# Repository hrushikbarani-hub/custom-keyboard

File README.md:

# NEXUS 2x3 Wired Macro Pad

A compact six-key wired macro pad with a small I2C OLED screen.

## Design direction

- Layout: 2 rows x 3 columns, six MX-style keys
- Controller: Hack Club Orpheus Pico 2, USB-C, Pico-compatible footprint
- Display: Waveshare 0.91-inch OLED SKU 14657, SSD1306 128x32, GP4/GP5
- Firmware: USB HID macro layers
- PCB: custom KiCad board
- Case: two-piece 3D-printed case

## Initial layers

NEXUS: Wake PC, open NEXUS, display standby, microphone toggle, Jellyfin, Pi-hole/Tailscale status.

Media: previous, play/pause, next, volume down, volume up, mute.

## Build status

- [x] Concept, layout, pin budget, BOM, and grant draft
- [x] Confirm exact controller, OLED, switch, and socket part numbers
- [x] KiCad schematic (ERC clean)
- [x] PCB routing (DRC/connectivity/parity clean)
- [x] Case CAD (v1.1; physical fit pending)
- [x] Firmware source prepared
- [ ] Physical assembly and testing

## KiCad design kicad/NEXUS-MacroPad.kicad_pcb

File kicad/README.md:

# NEXUS 2x3 macro pad — KiCad 10

Open `NEXUS-MacroPad.kicad_pro`. Editable schematic, fully routed two-layer PCB, and project-local footprints are included. `manufacturing/` contains the two copper layers, both masks and silkscreens, board outline, and separate plated/non-plated Excellon drills. No solder-paste files are needed for this through-hole design.

## Fabrication and assembly

- PCB: 60 x 66 mm bounding box; chamfered outline with two OLED clamp reliefs. Two copper layers, 1.6 mm FR4, 0.25 mm traces/clearance, 0.8/0.4 mm vias. Order only after confirming the selected hardware dimensions.
- Six PCB-mount Cherry-MX-compatible switches, 19.05 mm pitch. Plate mounting supplies mechanical retention; switch solder joints locate the PCB. No independent PCB mounting screws are used.
- Six 1N4148 DO-35 diodes with 7.62 mm lead pitch. Cathode/band is the square pad and goes to the row. Front keys are SW1–3; rear keys SW4–6.
- Non-wireless Pico-compatible module socketed **under** the board, component side facing the case floor, USB facing the rear. Use two 1x20, 2.54 mm socket strips plus matching module headers. The host-board footprint courtyard describes socket rows, not the elevated underside module body. Do not install a Pico W: its antenna clearance is not provided.
- J1 is four direct-solder wire pads, not a header or a direct OLED-module footprint. Pin 1 GND, pin 2 3.3 V, pin 3 SCL, pin 4 SDA. Check the actual OLED pin order; use 3.3 V only. Solder insulated flexible leads directly to the pads and provide strain relief. Do not fit a vertical header: it would hit the lid. Keep solder/wire height below 1.2 mm above the PCB.
- R1 and R2 are optional 4.7k through-hole pullups on the PCB underside, marked DNP. Leave them empty if the display already has I2C pullups; populate only if needed. Top-side mounting would overlap the OLED envelope.
- Avoid long switch/diode leads on the underside where they approach the raised controller. Trim and inspect before inserting the module. Do not connect an external 5 V supply.

## Firmware pin assignment

| Function | GPIO | Pico physical pad |
|---|---|---|
| OLED SDA | GP4 | 6 |
| OLED SCL | GP5 | 7 |
| Front row ROW0 | GP6 | 9 |
| Rear row ROW1 | GP7 | 10 |
| Left column COL0 | GP8 | 11 |
| Middle column COL1 | GP9 | 12 |
| Right column COL2 | GP10 | 14 |

Scan rows low with column input pullups (COL2ROW). The schematic deliberately leaves unused module pins unconnected. Pico module ground pads are internally common; all seven carrier ground pads are also routed.

## Case compatibility and limits

Use the revised **v1.2** case in the [Onshape document](https://cad.onshape.com/documents/93b46cd1c225a7c1c0317dbe/w/328820a536ad539164365b4e/e/89c11f70e4b29e71ba5d3f40). The old v1 OLED bridge is superseded by two side clamps, which clear the PCB reliefs. Six underside diode pockets provide clearance after correcting the switch stack. Four printed bodies: base, plate, two clamps. Older case exports are superseded.

Case coordinates are front-left origin. PCB X = 100 + case X; PCB Y = 178 - case Y. Assembled PCB top is case Z = 21 mm, bottom 19.4 mm; the plate top is Z = 26 mm, and the local underside Z = 24.5 mm. MX seating uses 5 mm from plate TOP to PCB top (3.5 mm below the 1.5 mm clip region). STEP uses XY aligned to the case and requires a +21 mm Z translation. The earlier 19.5/17.9 mm stack was incorrect and is superseded. See the [Cherry mechanical drawing](https://www.farnell.com/datasheets/1792245.pdf), mounting options on page 2.

The STEP uses a generic Raspberry Pi Pico, not the exact USB-C Orpheus board. Installed MX switch 3D models are missing; their native footprint geometry is present. Onshape now checks the exact PCB outline plus 20 nominal electronics envelopes against the case and each other. The USB-plug/controller bounding-box overlap is intentionally excluded because a plug engages the connector; exact connector mating is not modeled. Nominal checks passed, but these are not a tolerance analysis or an exact component assembly. Actual socket height, USB plug, OLED module, switch variant, and insert pilot still require confirmation. No physical prototype has been tested. Toggle 'Show electronics fit envelopes' in the case feature to inspect; keep it OFF for printing/exporting case parts.

KiCad ERC, DRC, connectivity, and schematic-to-PCB parity reports are included. No reported issues were suppressed to obtain a pass. Manufacturing exports are design outputs, not an instruction to order without the above checks.

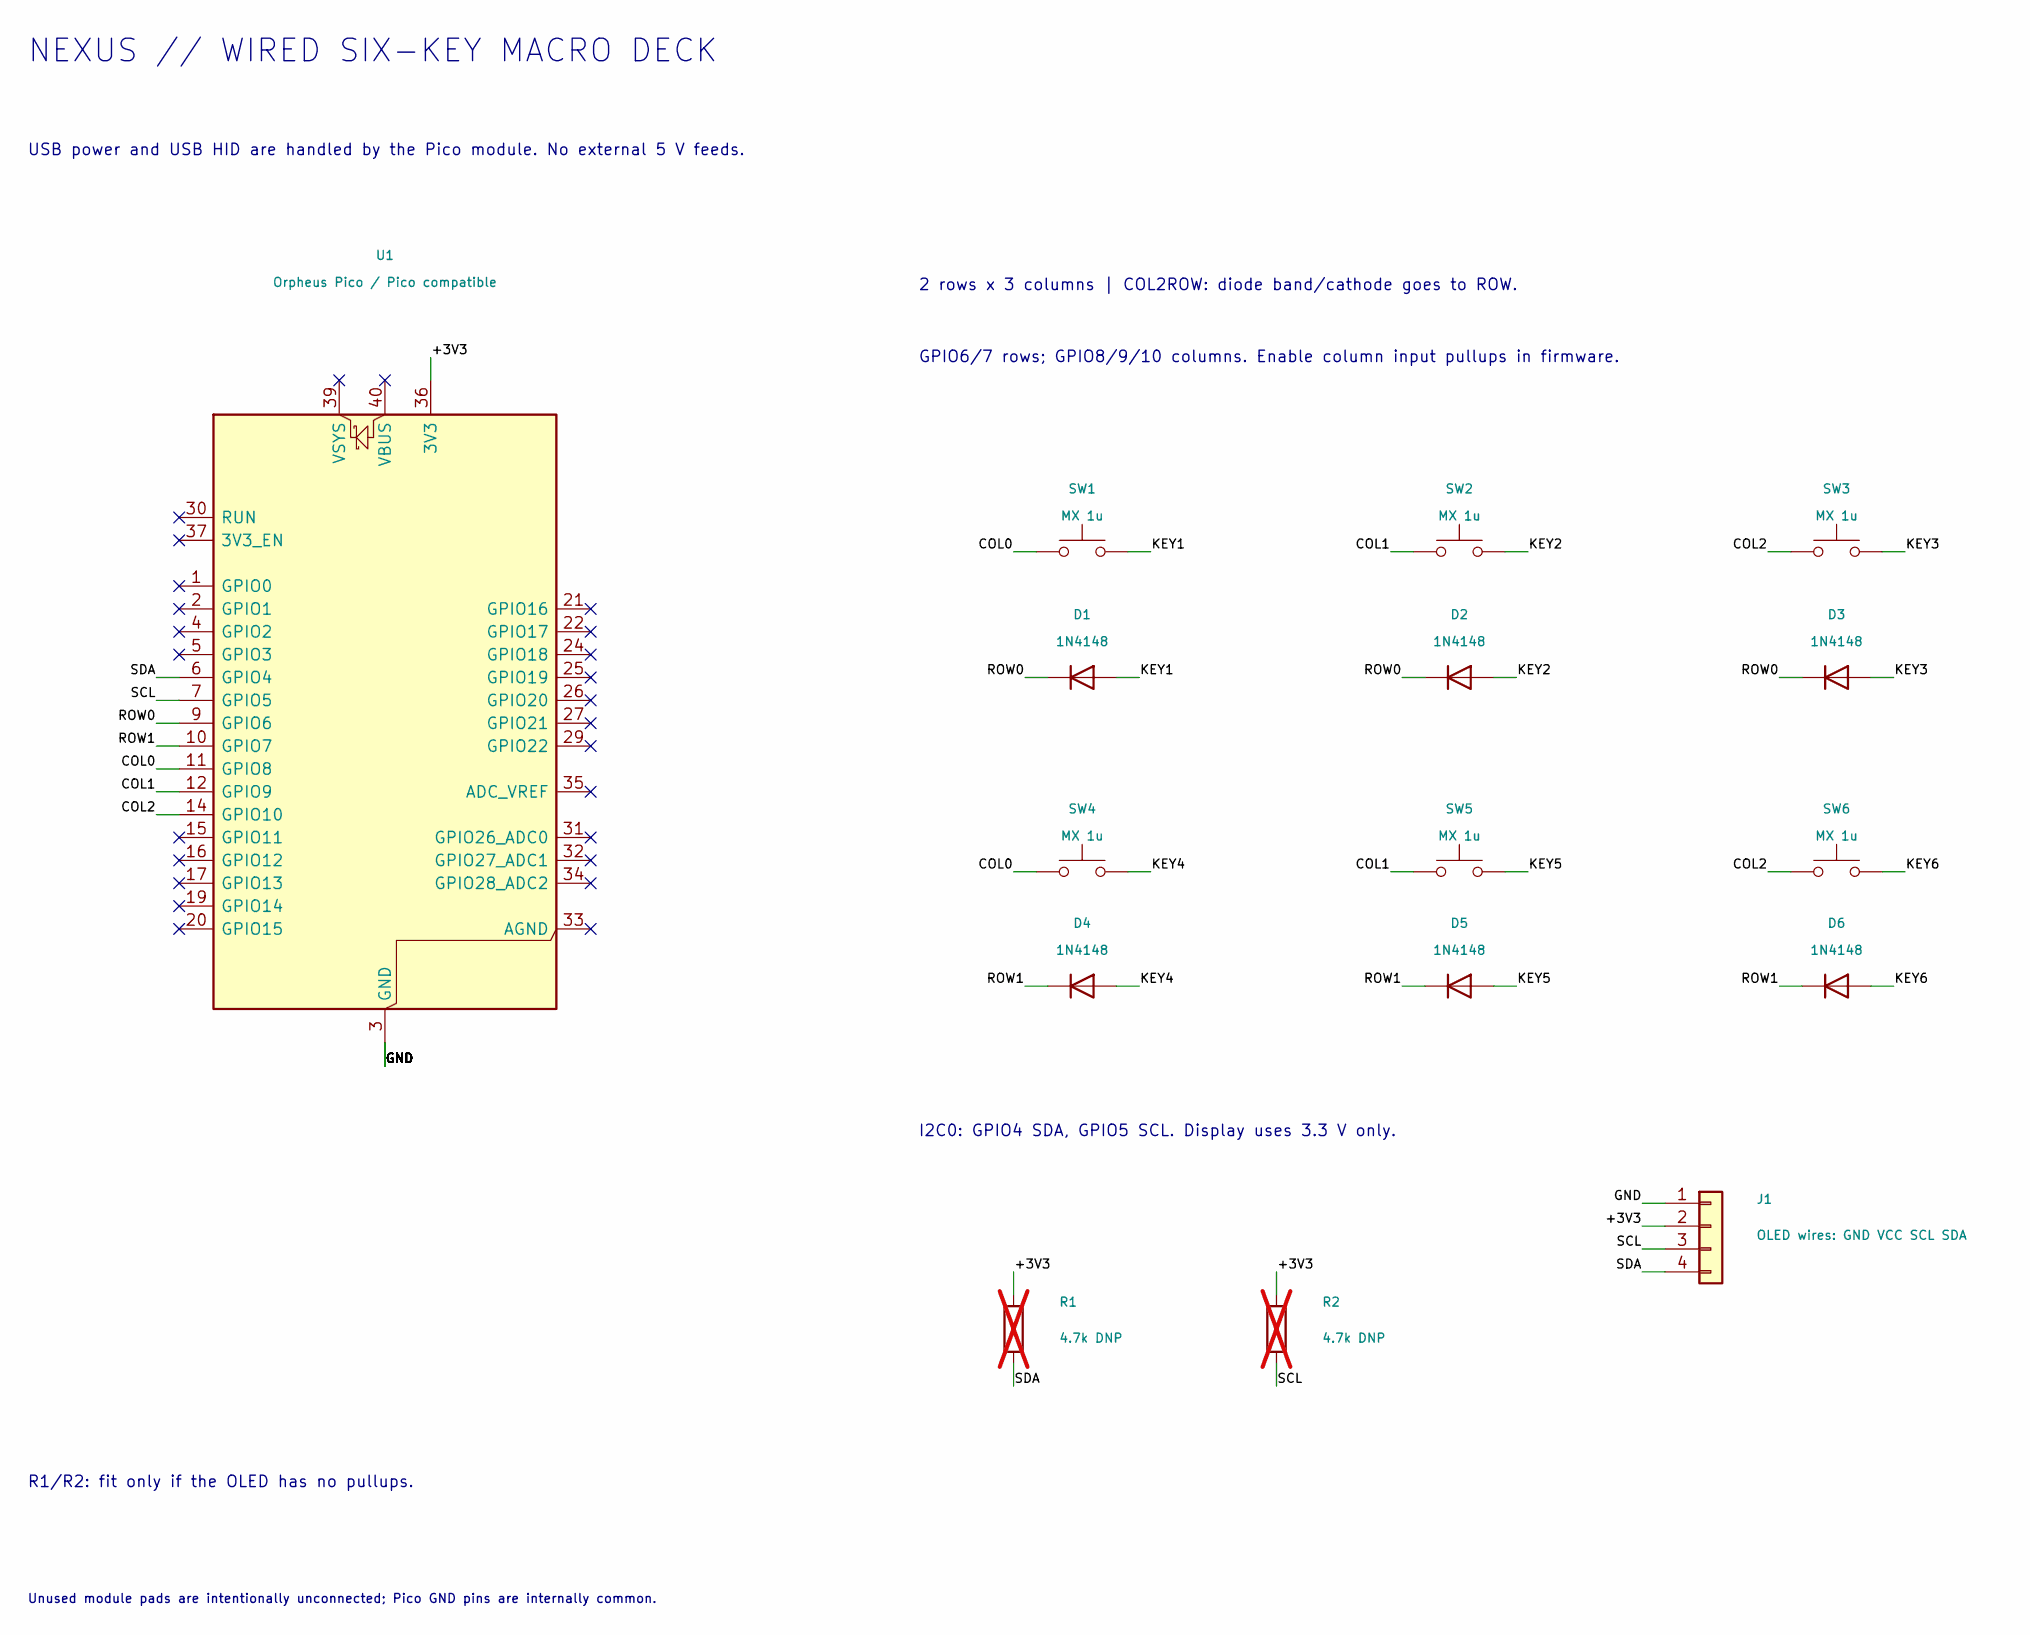
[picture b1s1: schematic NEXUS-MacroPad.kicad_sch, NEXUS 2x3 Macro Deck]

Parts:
D1, D2, D3, D4, D5, D6: 1N4148; D_1N4148
J1: OLED wires: GND VCC SCL SDA; OLED_WirePads
R1, R2: 4.7k DNP; R_Axial_DIN0207_L6.3mm_D2.5mm_P7.62mm_Horizontal; not fitted
SW1, SW2, SW3, SW4, SW5, SW6: MX 1u; MX_1u
U1: Orpheus Pico / Pico compatible; Pico_Underside_Carrier

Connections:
/+3V3: J1.2, R1.1, R2.1, U1.36 (3V3)
/COL0: SW1.1, SW4.1, U1.11 (GPIO8)
/COL1: SW2.1, SW5.1, U1.12 (GPIO9)
/COL2: SW3.1, SW6.1, U1.14 (GPIO10)
/GND: J1.1, U1.3 (GND), U1.8 (GND), U1.13 (GND), U1.18 (GND), U1.23 (GND), U1.28 (GND), U1.38 (GND)
/KEY1: D1.2 (A), SW1.2
/KEY2: D2.2 (A), SW2.2
/KEY3: D3.2 (A), SW3.2
/KEY4: D4.2 (A), SW4.2
/KEY5: D5.2 (A), SW5.2
/KEY6: D6.2 (A), SW6.2
/ROW0: D1.1 (K), D2.1 (K), D3.1 (K), U1.9 (GPIO6)
/ROW1: D4.1 (K), D5.1 (K), D6.1 (K), U1.10 (GPIO7)
/SCL: J1.3, R2.2, U1.7 (GPIO5)
/SDA: J1.4, R1.2, U1.6 (GPIO4)

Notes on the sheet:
NEXUS // WIRED SIX-KEY MACRO DECK
USB power and USB HID are handled by the Pico module. No external 5 V feeds.
2 rows x 3 columns | COL2ROW: diode band/cathode goes to ROW.
GPIO6/7 rows; GPIO8/9/10 columns. Enable column input pullups in firmware.
I2C0: GPIO4 SDA, GPIO5 SCL. Display uses 3.3 V only.
R1/R2: fit only if the OLED has no pullups.
Unused module pads are intentionally unconnected; Pico GND pins are internally common.

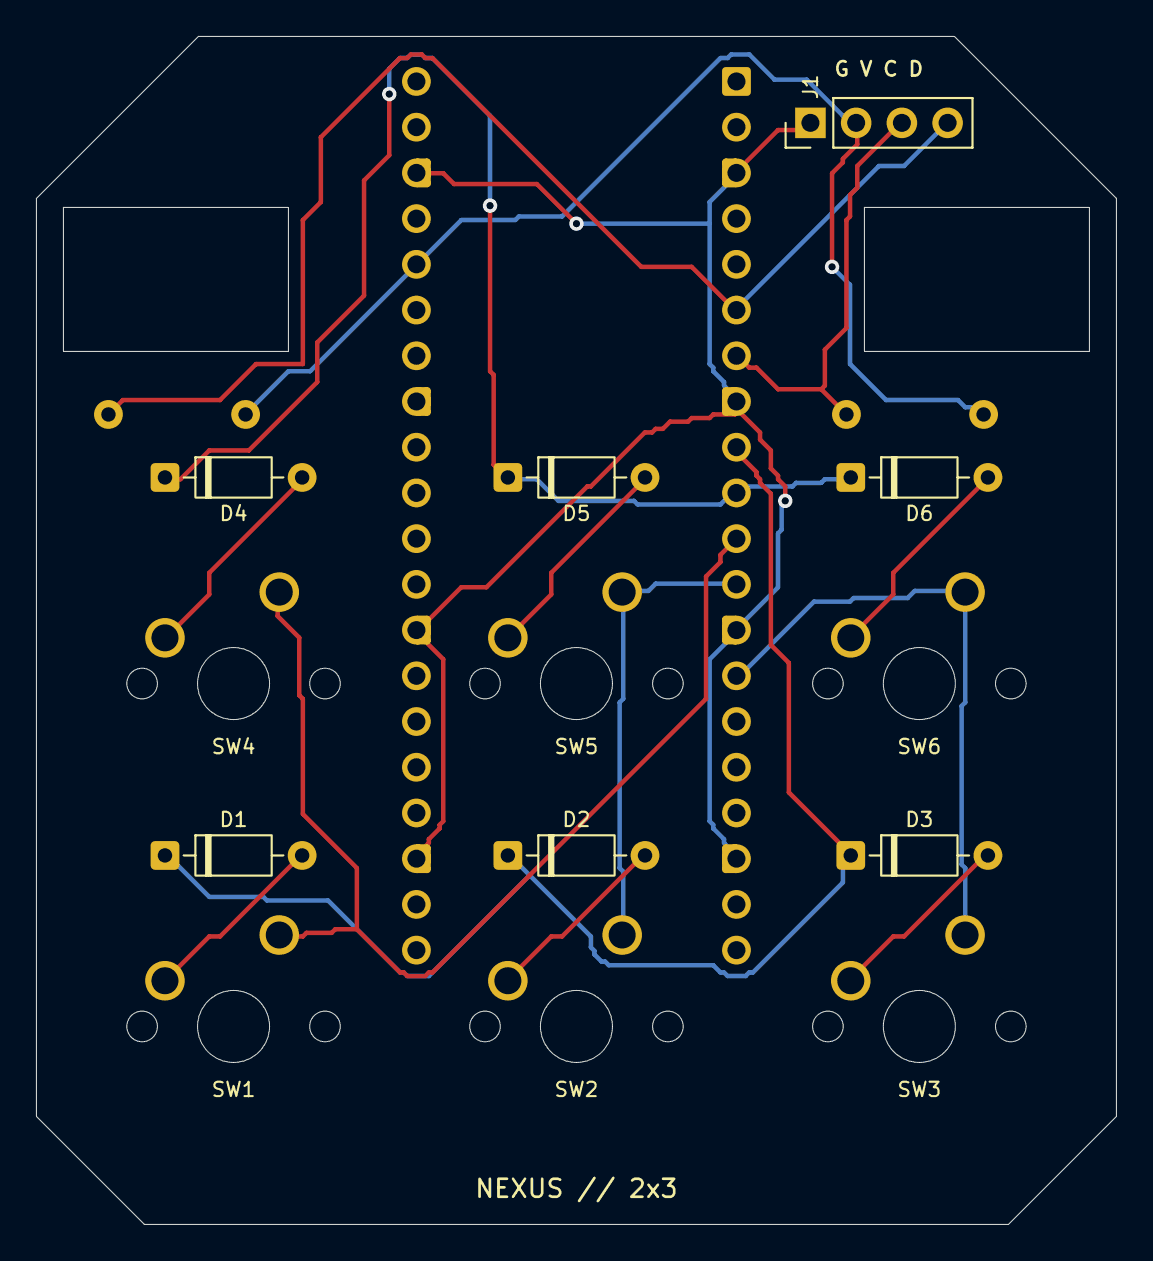
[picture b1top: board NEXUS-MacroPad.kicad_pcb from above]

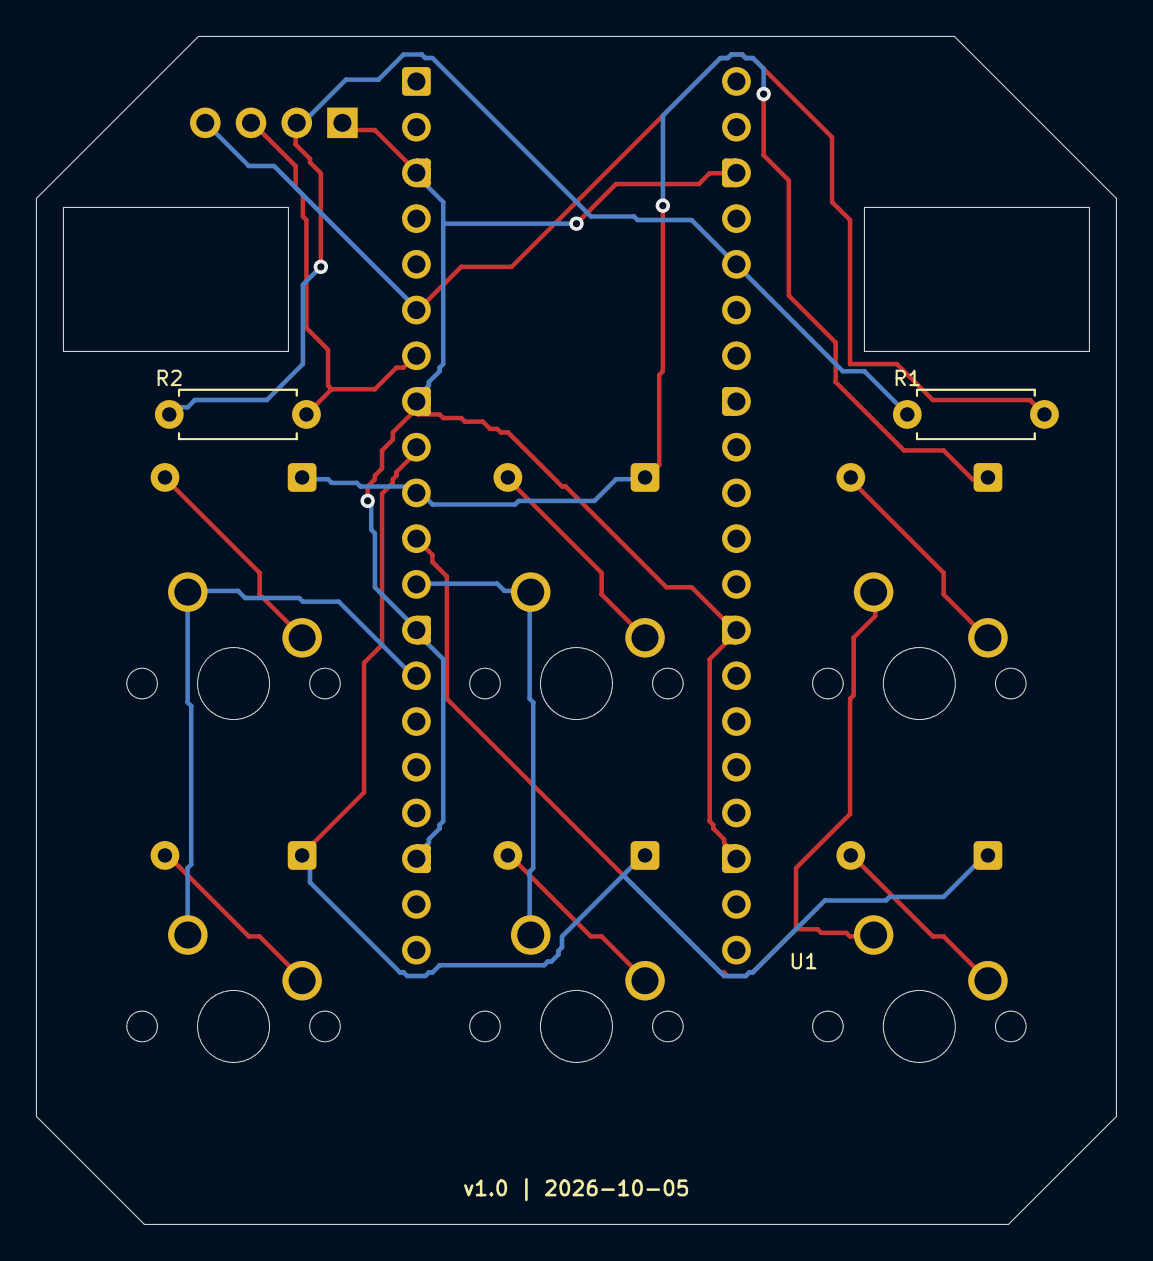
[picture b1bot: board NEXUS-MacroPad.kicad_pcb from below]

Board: 2 copper layers, 60.0 x 66.0 mm, 16 parts (3 on the bottom side), 15 nets.
